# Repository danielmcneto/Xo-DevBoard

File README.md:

# Xo-DevBoard

**Xo-DevBoard** is a compact, custom ESP32-WROOM-32 development board featuring an integrated display header designed specifically for real-time sensor debugging without relying on a tethered PC monitor.

---

## The Problem & The Solution

**Tired of constantly alt-tabbing to your Serial Monitor just to check if a sensor value is updating?**  
Traditional devboards force you to keep your laptop plugged in during basic hardware debugging. The **Xo-DevBoard** solves this by providing a dedicated display interface directly on the board. Plug in a mini OLED or TFT screen, flash your code, and read live telemetry anywhere—completely standalone.

---

## Features & Hardware Highlights

* **Brain:** ESP32-WROOM-32 module (Wi-Fi + Bluetooth BLE).
* **Integrated Display Interface:** Dedicated 8-pin connector supporting I2C/SPI display modules.
* **On-board USB-to-UART Converter:** CH340C chip with an automated DTR/RTS auto-reset circuit
* **Power Management:** Modern USB-C connector with ESD/overcurrent protection.
* **User Controls:** Tactile Reset (EN) and Boot (GPIO0) buttons.
* **Full Breakout:** One 1x15 pin header and one 1x10 pin header breaking out all usable ESP32 GPIOs for breadboard prototyping.

---

Display Header Pinout

The built-in display connector is routed to the following ESP32 pins:

| Pin # | Header Label | ESP32 GPIO | Typical Usage (I2C / SPI) |
| :---: | :----------: | :--------: | :-----------------------: |
| 1     | GND          | GND        | Ground               |
| 2     | 3.3V         | +3.3VA     | Power Supply (3.3V)    |
| 3     | D18          | GPIO18     | SDA (I2C) / MOSI (SPI)   |
| 4     | D23          | GPIO23     | SCL (I2C) / SCK (SPI)    |
| 5     | D2           | GPIO02     | Reset / General IO      |
| 6     | D4           | GPIO04     | Data / Command (DC)    |
| 7     | D5           | GPIO05     | Chip Select (CS)        |
| 8     | 3.3V         | +3.3VA     | Auxiliary Power         |

## Project Status & Firmware

This repository contains:
1. **KiCad Production Files:** Schematic (`.kicad_sch`), PCB layout (`.kicad_pcb`), and Gerber files for manufacturing.
2. **Starter Firmware:** A C++/PlatformIO demo program that initializes the display, tests onboard peripherals, and renders a `"Hello World!"` on the screen.

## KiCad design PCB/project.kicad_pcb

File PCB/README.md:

## Here you will find the files of the pcb

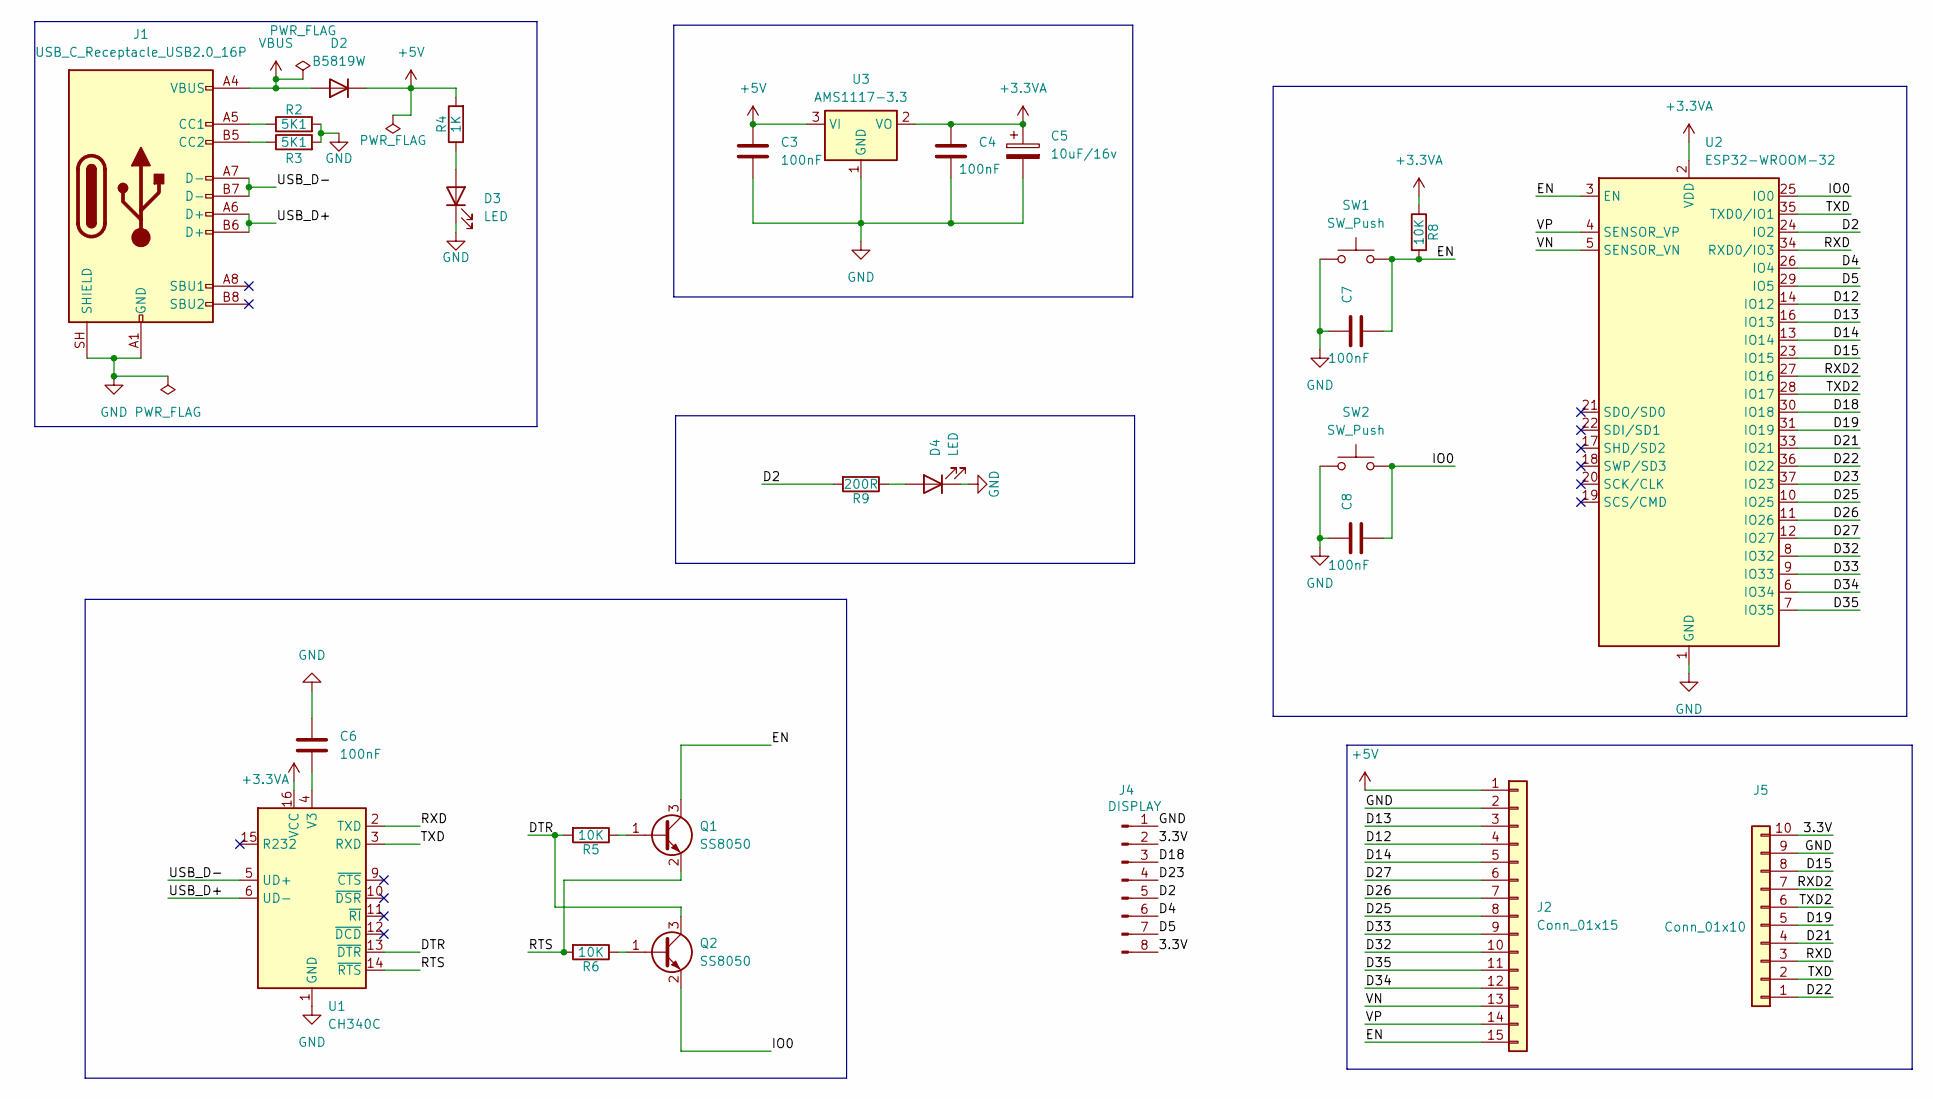
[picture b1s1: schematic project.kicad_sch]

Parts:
C3, C4, C6, C7, C8: 100nF; C_0603_1608Metric
C5: 10uF/16v; CP_EIA-3216-10_Kemet-I
D2: B5819W; D_SOD-123
D3, D4: LED; LED_0603_1608Metric
J1: USB_C_Receptacle_USB2.0_16P; USB_C_Receptacle_GCT_USB4105-xx-A_16P_TopMnt_Horizontal
J2: Conn_01x15; PinHeader_1x15_P2.54mm_Vertical
J4: DISPLAY; PinSocket_1x08_P2.54mm_Vertical
J5: Conn_01x10; PinSocket_1x10_P2.54mm_Vertical
Q1, Q2: SS8050; SOT-23
R2, R3: 5K1; R_0603_1608Metric
R4: 1K; R_0603_1608Metric
R5, R6, R8: 10K; R_0603_1608Metric
R9: 200R; R_0603_1608Metric
SW1, SW2: SW_Push; SW_Push_SPST_NO_Alps_SKRK
U1: CH340C; SOIC-16_3.9x9.9mm_P1.27mm
U2: ESP32-WROOM-32
U3: AMS1117-3.3; SOT-223-3_TabPin2

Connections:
+3.3VA: C4.1, C5.1, R8.1, U1.16 (VCC), U2.2 (VDD), U3.2 (VO)
+5V: C3.1, D2.1 (K), J2.1, R4.2, U3.3 (VI)
/3.3V: J4.2, J4.8, J5.10
/D2: J4.5, R9.2, U2.24 (IO2)
/D4: J4.6, U2.26 (IO4)
/D5: J4.7, U2.29 (IO5)
/D12: J2.4, U2.14 (IO12)
/D13: J2.3, U2.16 (IO13)
/D14: J2.5, U2.13 (IO14)
/D15: J5.8, U2.23 (IO15)
/D18: J4.3, U2.30 (IO18)
/D19: J5.5, U2.31 (IO19)
/D21: J5.4, U2.33 (IO21)
/D22: J5.1, U2.36 (IO22)
/D23: J4.4, U2.37 (IO23)
/D25: J2.8, U2.10 (IO25)
/D26: J2.7, U2.11 (IO26)
/D27: J2.6, U2.12 (IO27)
/D32: J2.10, U2.8 (IO32)
/D33: J2.9, U2.9 (IO33)
/D34: J2.12, U2.6 (IO34)
/D35: J2.11, U2.7 (IO35)
/DTR: Q2.3 (C), R5.2, U1.13 (~DTR)
/EN: C7.2, J2.15, Q1.3 (C), R8.2, SW1.2, U2.3 (EN)
/IO0: C8.2, Q2.2 (E), SW2.2, U2.25 (IO0)
/RTS: Q1.2 (E), R6.2, U1.14 (~RTS)
/RXD: J5.3, U1.2 (TXD), U2.34 (RXD0/IO3)
/RXD2: J5.7, U2.27 (IO16)
/TXD: J5.2, U1.3 (RXD), U2.35 (TXD0/IO1)
/TXD2: J5.6, U2.28 (IO17)
/USB_D+: J1.A6 (D+), J1.B6 (D+), U1.6 (UD-)
/USB_D-: J1.A7 (D-), J1.B7 (D-), U1.5 (UD+)
/VN: J2.13, U2.5 (SENSOR_VN)
/VP: J2.14, U2.4 (SENSOR_VP)
GND: C3.2, C4.2, C5.2, C6.1, C7.1, C8.1, D3.1 (K), D4.1 (K), J1.A1 (GND), J1.A12 (GND), J1.B1 (GND), J1.B12 (GND), J1.SH (SHIELD), J2.2, J4.1, J5.9, R2.2, R3.2, SW1.1, SW2.1, U1.1 (GND), U2.1 (GND), U2.15 (GND), U2.38 (GND), U2.39 (GND), U3.1 (GND)
unnamed: D3.2 (A), R4.1
unnamed: D4.2 (A), R9.1
unnamed: J1.A5 (CC1), R2.1
unnamed: J1.B5 (CC2), R3.1
unnamed: Q1.1 (B), R5.1
unnamed: Q2.1 (B), R6.1
unnamed: C6.2, U1.4 (V3)
VBUS: D2.2 (A), J1.A4 (VBUS), J1.A9 (VBUS), J1.B4 (VBUS), J1.B9 (VBUS)

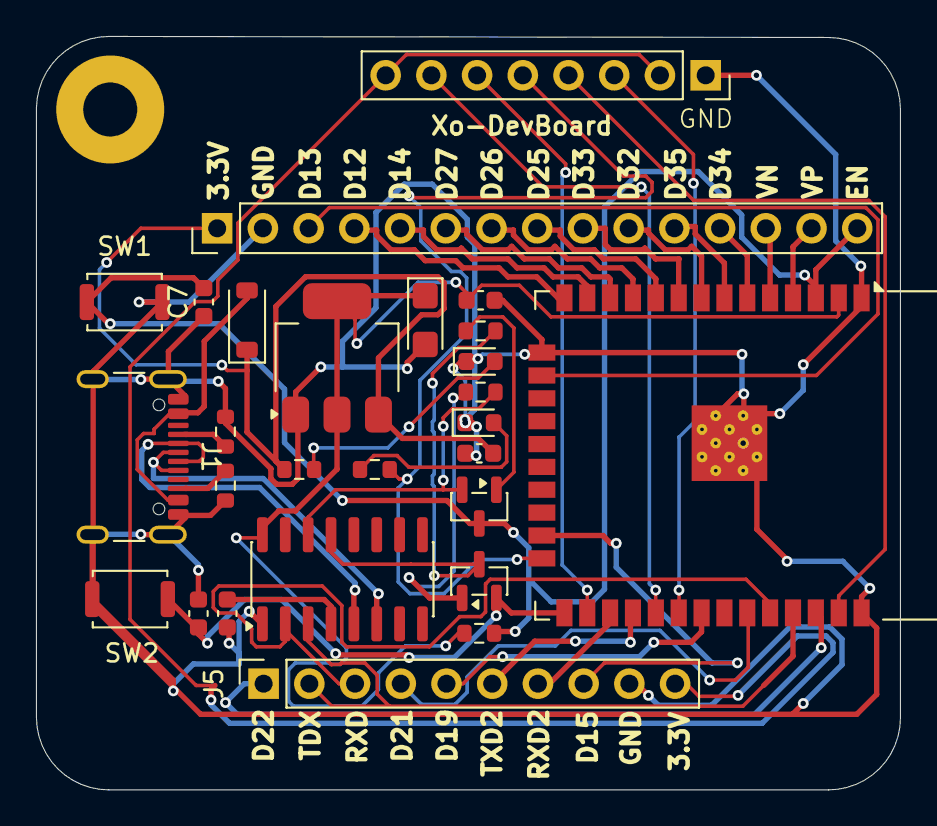
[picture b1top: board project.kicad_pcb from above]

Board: 2 copper layers, 48.0 x 41.9 mm, 28 parts (1 on the bottom side), 43 nets.

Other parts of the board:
THAT SHIT WAS HARD TO BUILT: LOGO; draw

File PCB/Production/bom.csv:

Designator,Footprint,Quantity,Value,LCSC Part #
"C3, C4, C6, C7, C8",0603,5,100nF,
C5,CP_EIA-3216-10_Kemet-I,1,10uF/16v,
D2,D_SOD-123,1,B5819W,
"D3, D4",0603,2,LED,
J1,USB_C_Receptacle_GCT_USB4105-xx-A_16P_TopMnt_Horizontal,1,USB_C_Receptacle_USB2.0_16P,
J2,PinHeader_1x15_P2.54mm_Vertical,1,Conn_01x15,
J4,PinSocket_1x08_P2.54mm_Vertical,1,DISPLAY,
J5,PinSocket_1x10_P2.54mm_Vertical,1,Conn_01x10,
"Q1, Q2",SOT-23,2,SS8050,
"R2, R3",0603,2,5K1,
R4,0603,1,1K,
"R5, R6, R8",0603,3,10K,
R9,0603,1,200R,
"SW1, SW2",SW_Push_SPST_NO_Alps_SKRK,2,SW_Push,
U1,SOIC-16_3.9x9.9mm_P1.27mm,1,CH340C,
U2,ESP32-WROOM-32,1,ESP32-WROOM-32,
U3,SOT-223-3_TabPin2,1,AMS1117-3.3,
